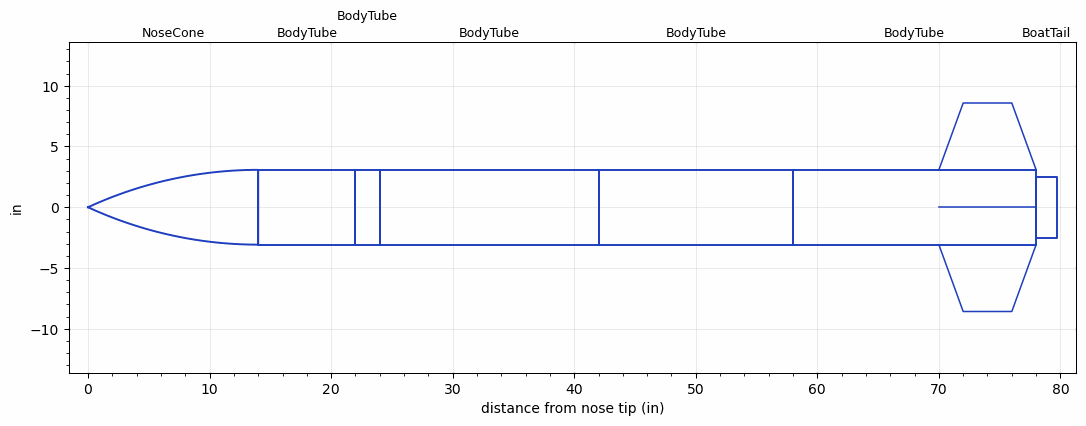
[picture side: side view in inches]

<RASAeroDocument>
 <FileVersion>2</FileVersion>
 <RocketDesign>
  <NoseCone>
   <Length>14</Length>
   <Diameter>6.154</Diameter>
   <Shape>Tangent Ogive</Shape>
   <Location>0</Location>
  </NoseCone>
  <BodyTube>
   <Length>8</Length>
   <Diameter>6.154</Diameter>
   <Location>14</Location>
  </BodyTube>
  <BodyTube>
   <Length>2</Length>
   <Diameter>6.154</Diameter>
   <Location>22</Location>
  </BodyTube>
  <BodyTube>
   <Length>18</Length>
   <Diameter>6.154</Diameter>
   <Location>24</Location>
  </BodyTube>
  <BodyTube>
   <Length>16</Length>
   <Diameter>6.154</Diameter>
   <RailGuideDiameter>0.3819</RailGuideDiameter>
   <RailGuideHeight>0.3819</RailGuideHeight>
   <Location>41.9999</Location>
  </BodyTube>
  <BodyTube>
   <Length>20</Length>
   <Diameter>6.154</Diameter>
   <RailGuideDiameter>0.3819</RailGuideDiameter>
   <RailGuideHeight>0.3819</RailGuideHeight>
   <Location>57.9999</Location>
   <Fin>
    <Count>4</Count>
    <Chord>8</Chord>
    <Span>5.5</Span>
    <SweepDistance>2</SweepDistance>
    <TipChord>4</TipChord>
    <Thickness>0.125</Thickness>
    <Location>8</Location>
    <AirfoilSection>Rounded</AirfoilSection>
   </Fin>
  </BodyTube>
  <BoatTail>
   <Length>1.7</Length>
   <Diameter>5</Diameter>
   <RearDiameter>5</RearDiameter>
   <Location>77.9998</Location>
  </BoatTail>
  <Surface>Sheet Metal</Surface>
  <CD>0</CD>
  <ModifiedBarrowman>False</ModifiedBarrowman>
  <Turbulence>False</Turbulence>
  <UseBooster1>False</UseBooster1>
  <UseBooster2>False</UseBooster2>
 </RocketDesign>
 <LaunchSite>
  <Altitude>889.1076</Altitude>
  <Pressure>28.9828</Pressure>
  <RodAngle>5</RodAngle>
  <RodLength>71.9999</RodLength>
  <Temperature>55.8293</Temperature>
  <WindSpeed>15</WindSpeed>
 </LaunchSite>
 <Recovery>
  <Altitude1>656.168</Altitude1>
  <Altitude2>0</Altitude2>
  <DeviceType1>Parachute</DeviceType1>
  <DeviceType2>None</DeviceType2>
  <Event1>True</Event1>
  <Event2>False</Event2>
  <Size1>59.9999</Size1>
  <Size2>0</Size2>
  <EventType1>Altitude</EventType1>
  <EventType2>None</EventType2>
  <CD1>1.1</CD1>
  <CD2>0</CD2>
 </Recovery>
 <SimulationList>
  <Simulation>
   <SustainerLaunchWt>25.1967</SustainerLaunchWt>
   <SustainerCG>44.5519</SustainerCG>
   <SustainerIgnitionDelay>0</SustainerIgnitionDelay>
   <Booster1SeparationDelay>0</Booster1SeparationDelay>
   <Booster1IgnitionDelay>0</Booster1IgnitionDelay>
   <IncludeBooster1>False</IncludeBooster1>
   <Booster2Delay>0</Booster2Delay>
   <IncludeBooster2>False</IncludeBooster2>
  </Simulation>
 </SimulationList>
</RASAeroDocument>
